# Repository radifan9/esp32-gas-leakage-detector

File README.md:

# Laporan Akhir Embedded System: Gas Leak Detection (GLD)

The project deals with the design and implementation of a gas leak detection system for safety measures. 

## Key Devices and Modules

- **ESP32 C3**: This is the main module making use of several pins/ports for interfacing with the other modules. 

- **MQ 2 Gas Sensor**: It is employed for the detection of gas leaks. Its Analog Out is connected to GPIO 5.

- **4x4 Keypad (PCF8574)**: It allows the user to enter WiFi credentials. It's connected to the ESP32 via I2C at address 0x38 and SDA: D21, SCL: D22.

- **16x2 Character LCD (HLF8574)**: Serves as a user interface displaying system status, like WiFi connection. It's connected to the ESP32 via I2C at address 0x27 and SDA: D21, SCL: D22.

- **Buzzer**: It is used for audible alarms during leaks. The Buzzer is driven by GPIO 10.

- **Power Gating MQ 2**: Enables power supply to MQ 2 Gas Sensor through GPIO 7.

## Software and Libraries Used:

- Arduino IDE
- <Wire.h> and <LiquidCrystal_I2C.h> libraries for interfacing with the I2C devices (LCD and Keypad).
- <esp_task_wdt.h> serving as the Watchdog Timer library.

## Sequence of Operation:

1. User at home inputs the SSID and password of the WiFi network on the 4x4 Keypad.
2. The entered credentials get authenticated.
3. If the WiFi connection is successful, the LCD displays "WiFi Connected". 

This setup allows the Gas Leak Detector (GLD) device to maintain connectivity with the Blynk app. Upon detection of a gas leak, the system triggers an alarm and reports the incident via Blynk to the smartphone user.

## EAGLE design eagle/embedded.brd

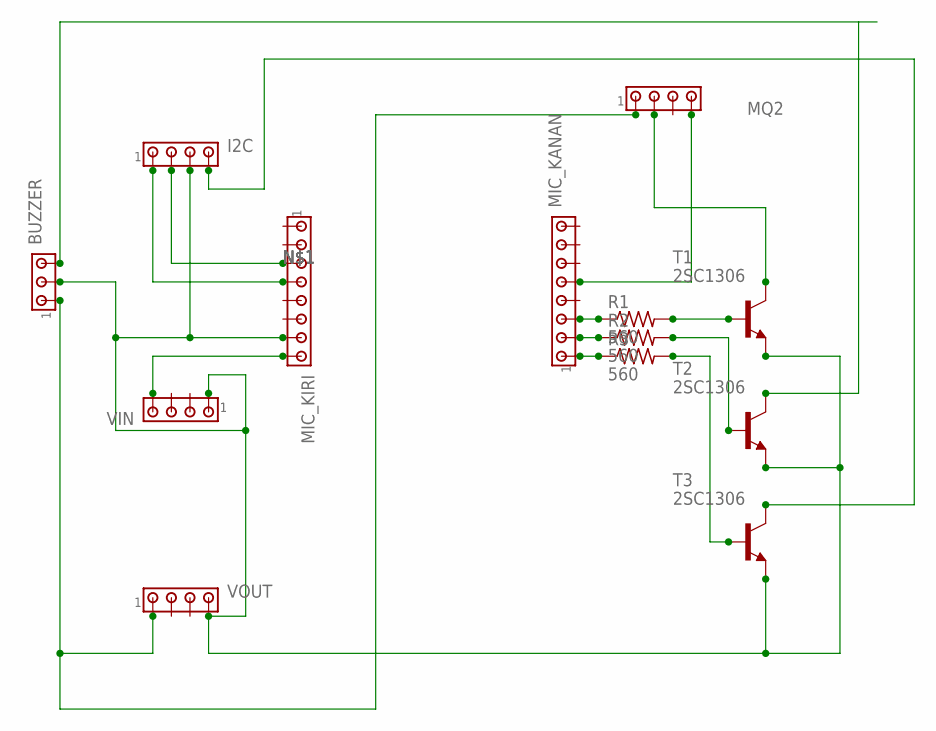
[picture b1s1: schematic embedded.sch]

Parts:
BUZZER: MTA03-100; 10X03MTA
I2C: MTA04-100; 10X04MTA
MIC_KANAN: MTA08-100; 10X08MTA
MIC_KIRI: MTA08-100; 10X08MTA
MQ2: MTA04-100; 10X04MTA
R1, R2, R3: 560; 0204/7
T1, T2, T3: 2SC1306; TO220BV
VIN: MTA04-100; 10X04MTA
VOUT: MTA04-100; 10X04MTA

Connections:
unnamed: I2C.2, MIC_KIRI.3
unnamed: BUZZER.2, I2C.3, MIC_KIRI.7, T1.3 (E), T2.3 (E), T3.3 (E), VIN.1, VOUT.4
unnamed: BUZZER.3, T2.2 (C)
unnamed: I2C.1, MIC_KIRI.4
unnamed: MIC_KIRI.8, VIN.4
unnamed: MIC_KANAN.3, R1.1
unnamed: MIC_KANAN.2, R2.1
unnamed: MIC_KANAN.1, R3.1
unnamed: BUZZER.1, MQ2.1, VOUT.1
unnamed: MQ2.2, T1.2 (C)
unnamed: MIC_KANAN.5, MQ2.4
unnamed: R1.2, T1.1 (B)
unnamed: R2.2, T2.1 (B)
unnamed: R3.2, T3.1 (B)
unnamed: I2C.4, T3.2 (C)

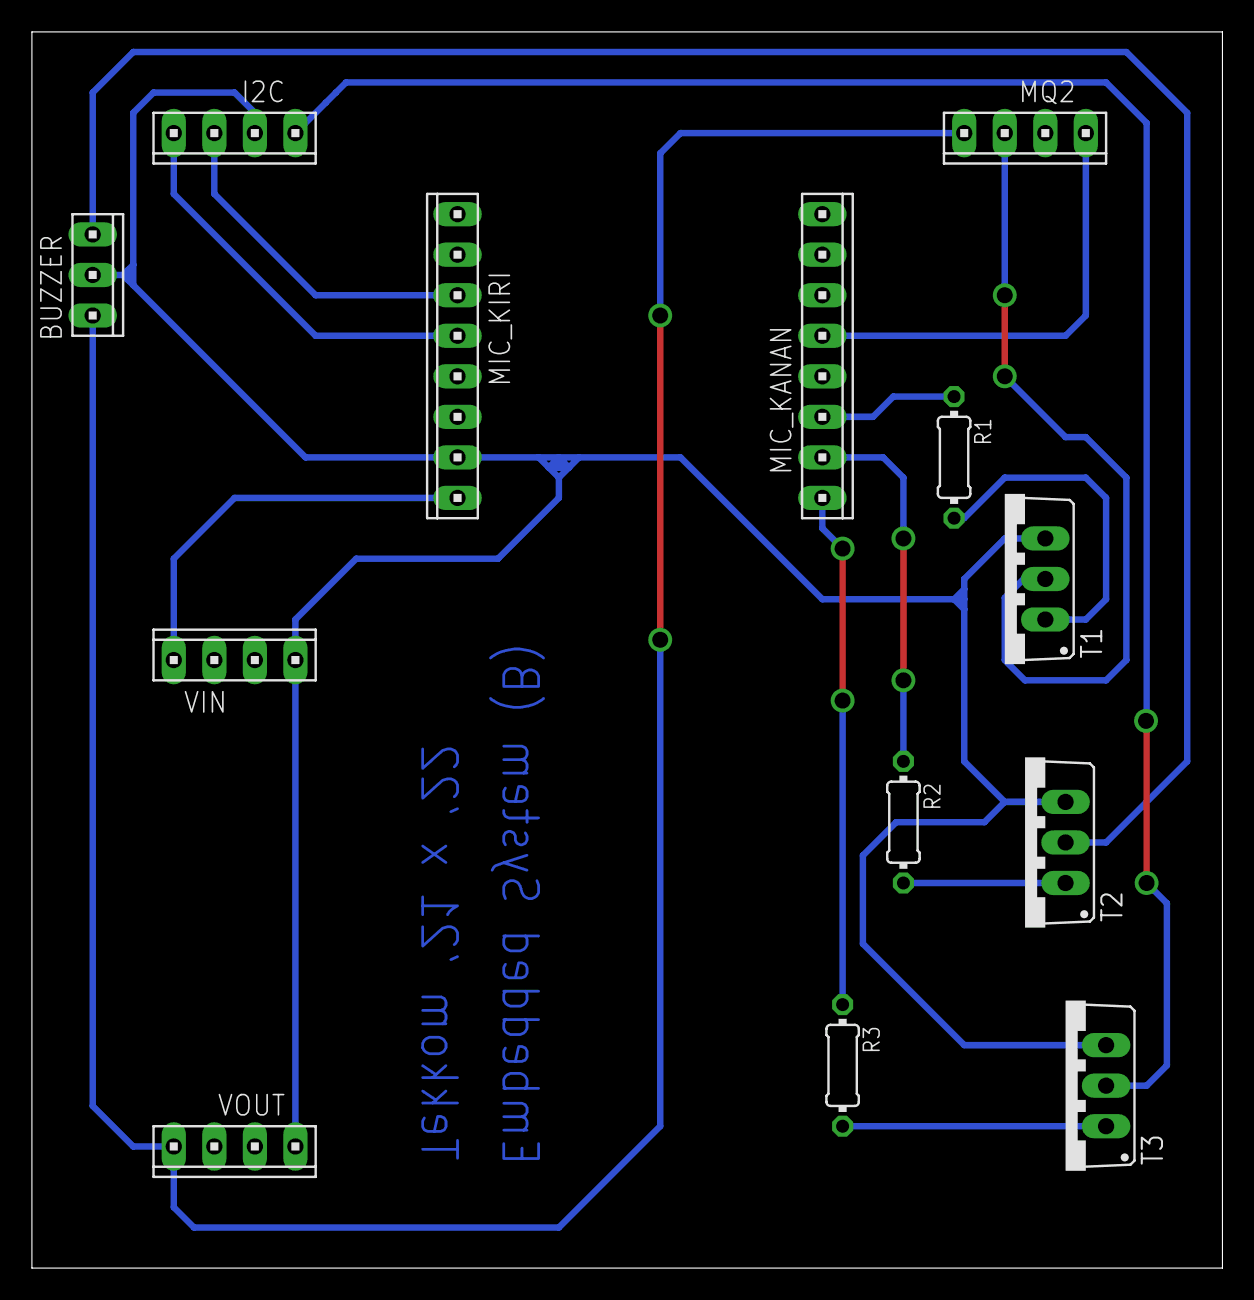
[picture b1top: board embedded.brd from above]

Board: 2 copper layers, 74.6 x 77.5 mm, 13 parts (0 on the bottom side), 15 nets.

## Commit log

2023-05-16 updated.
2023-05-21 widi_sensor_sleep
